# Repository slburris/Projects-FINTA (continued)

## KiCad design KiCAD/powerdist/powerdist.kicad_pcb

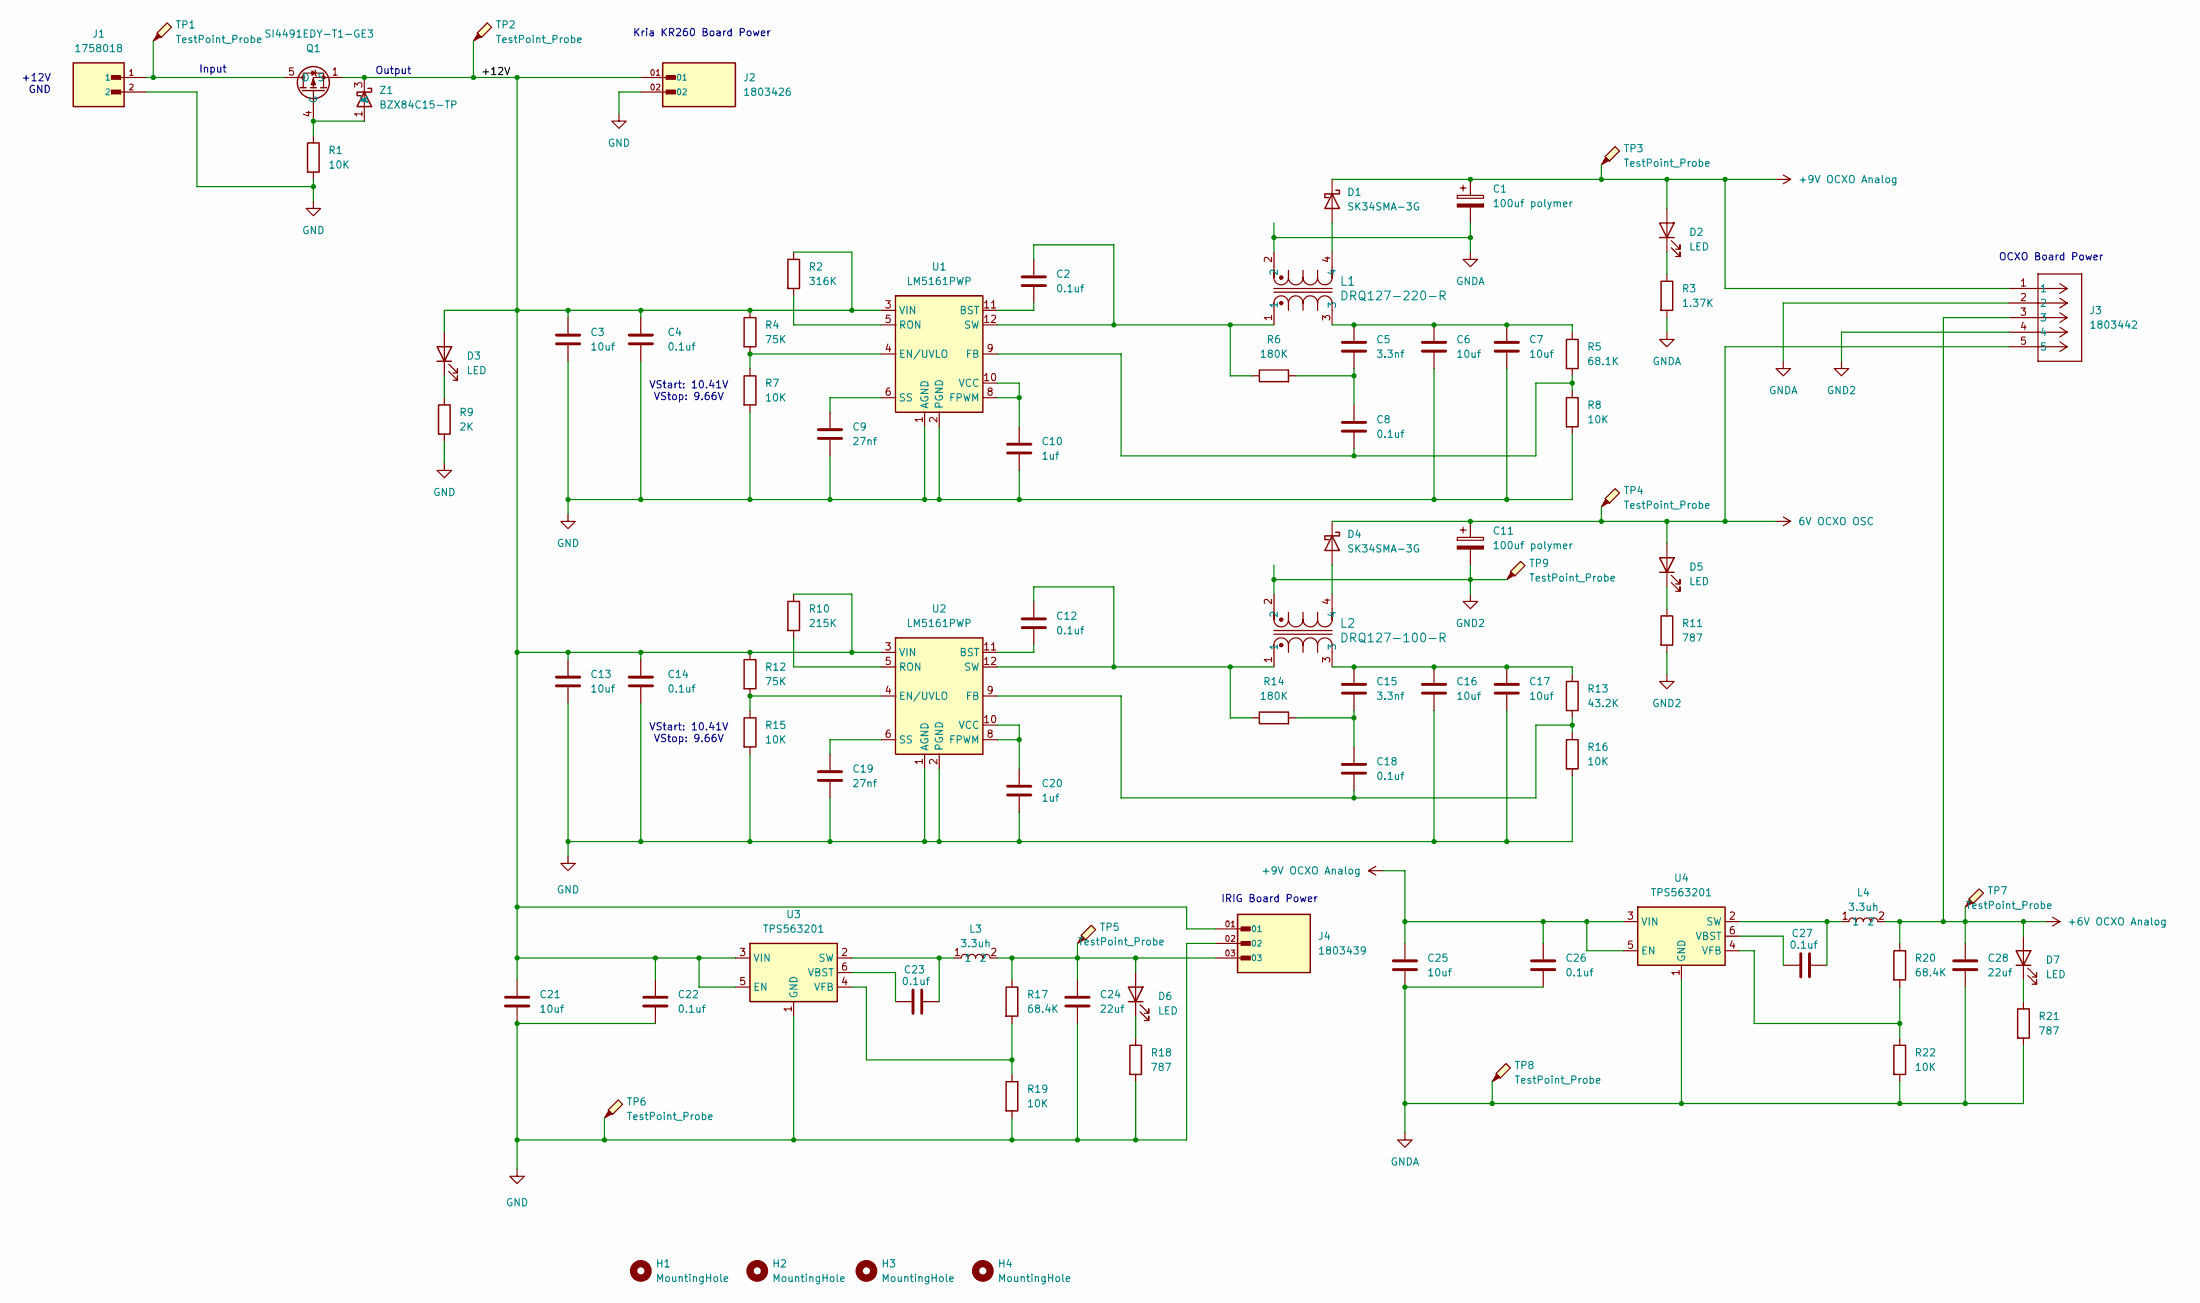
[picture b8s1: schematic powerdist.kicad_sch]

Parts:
C1, C11: 100uf polymer; CP_Radial_D5.0mm_P2.00mm
C2, C8, C12, C18: 0.1uf; C_0603_1608Metric_Pad1.08x0.95mm_HandSolder
C3, C6, C7, C13, C16, C17, C21, C25: 10uf; C_1206_3216Metric_Pad1.33x1.80mm_HandSolder
C4, C14, C22, C23, C26, C27: 0.1uf; C_1206_3216Metric_Pad1.33x1.80mm_HandSolder
C5, C15: 3.3nf; C_0603_1608Metric_Pad1.08x0.95mm_HandSolder
C9, C19: 27nf; C_0603_1608Metric_Pad1.08x0.95mm_HandSolder
C10, C20: 1uf; C_0603_1608Metric_Pad1.08x0.95mm_HandSolder
C24, C28: 22uf; C_1206_3216Metric_Pad1.33x1.80mm_HandSolder
D1, D4: SK34SMA-3G; D_SMA-SMB_Universal_Handsoldering
D2, D3, D5, D6, D7: LED; LED_0805_2012Metric_Pad1.15x1.40mm_HandSolder
H1, H2, H3, H4: MountingHole; MountingHole_5.3mm_M5
J1: 1758018; PHOENIX_1758018; PARTREV 10.07.2018
J2: 1803426; PHOENIX_1803426; PARTREV 25.02.2015
J3: 1803442; CONN_1803455; PARTREV 25.02.2015
J4: 1803439; PHOENIX_1803439; PARTREV 25.02.2015
L1: DRQ127-220-R; DRQ127
L2: DRQ127-100-R; DRQ127
L3, L4: 3.3uh; BCIHP10SC
Q1: SI4491EDY-T1-GE3; SOIC127P600X175-8N; Manufacturer_Part_Number SI4491EDY-T1-GE3
R1, R19, R22: 10K; R_1206_3216Metric_Pad1.30x1.75mm_HandSolder
R2: 316K; R_0603_1608Metric_Pad0.98x0.95mm_HandSolder
R3: 1.37K; R_1206_3216Metric_Pad1.30x1.75mm_HandSolder
R4, R12: 75K; R_0603_1608Metric_Pad0.98x0.95mm_HandSolder
R5: 68.1K; R_0603_1608Metric_Pad0.98x0.95mm_HandSolder
R6, R14: 180K; R_0603_1608Metric_Pad0.98x0.95mm_HandSolder
R7, R8, R15: 10K; R_0603_1608Metric_Pad0.98x0.95mm_HandSolder
R9: 2K; R_1206_3216Metric_Pad1.30x1.75mm_HandSolder
R10: 215K; R_0603_1608Metric_Pad0.98x0.95mm_HandSolder
R11, R18, R21: 787; R_1206_3216Metric_Pad1.30x1.75mm_HandSolder
R13: 43.2K; R_0805_2012Metric_Pad1.20x1.40mm_HandSolder
R16: 10K; R_0805_2012Metric_Pad1.20x1.40mm_HandSolder
R17, R20: 68.4K; R_1206_3216Metric_Pad1.30x1.75mm_HandSolder
TP1, TP2, TP3, TP4, TP5, TP6, TP7, TP8, TP9: TestPoint_Probe; TestPoint_Pad_2.0x2.0mm
U1, U2: LM5161PWP; Texas_HTSSOP-14-1EP_4.4x5mm_P0.65mm_EP3.4x5mm_Mask3.155x3.2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
U3, U4: TPS563201; SOT-23-6
Z1: BZX84C15-TP; SOT95P237X125-3N; Mouser Part Number 833-BZX84C15-TP

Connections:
6V OCXO OSC: C11.1, D4.1 (K), D5.2 (A), J3.5, TP4.1
+6V OCXO Analog: C28.1, D7.2 (A), J3.3, L4.2, R20.1, TP7.1
+9V OCXO Analog: C1.1, C25.1, C26.1, D1.1 (K), D2.2 (A), J3.1, TP3.1, U4.3 (VIN), U4.5 (EN)
/+12V: C3.1, C4.1, C13.1, C14.1, C21.1, C22.1, D3.2 (A), J2.01, J4.01, Q1.1 (S), Q1.2 (S), Q1.3 (S), R2.1, R4.1, R10.1, R12.1, TP2.1, U1.3 (VIN), U2.3 (VIN), U3.3 (VIN), U3.5 (EN), Z1.3 (K)
GND: C3.2, C4.2, C6.2, C7.2, C9.2, C10.2, C13.2, C14.2, C16.2, C17.2, C19.2, C20.2, C21.2, C22.2, C24.2, J1.2, J2.02, J4.02, R1.2, R7.2, R8.2, R9.2, R15.2, R16.2, R18.2, R19.2, TP6.1, U1.1 (AGND), U1.2 (PGND), U1.15 (AGND), U2.1 (AGND), U2.2 (PGND), U2.15 (AGND), U3.1 (GND)
GND2: C11.2, J3.4, L2.2, R11.2, TP9.1
GNDA: C1.2, C25.2, C26.2, C28.2, J3.2, L1.2, R3.2, R21.2, R22.2, TP8.1, U4.1 (GND)
unnamed: C2.1, L1.1, R6.1, U1.12 (SW), U1.13 (SW)
unnamed: C5.1, C6.1, C7.1, L1.3, R5.1
unnamed: C5.2, C8.1, R6.2
unnamed: C12.1, L2.1, R14.1, U2.12 (SW), U2.13 (SW)
unnamed: C15.1, C16.1, C17.1, L2.3, R13.1
unnamed: C15.2, C18.1, R14.2
unnamed: D1.2 (A), L1.4
unnamed: D2.1 (K), R3.1
unnamed: D3.1 (K), R9.1
unnamed: D4.2 (A), L2.4
unnamed: D5.1 (K), R11.1
unnamed: C24.1, D6.2 (A), J4.03, L3.2, R17.1, TP5.1
unnamed: D6.1 (K), R18.1
unnamed: D7.1 (K), R21.1
unnamed: J1.1, Q1.5 (D), Q1.6 (D), Q1.7 (D), Q1.8 (D), TP1.1
unnamed: Q1.4 (G), R1.1, Z1.1 (A)
unnamed: C2.2, U1.11 (BST)
unnamed: R4.2, R7.1, U1.4 (EN/UVLO)
unnamed: C8.2, R5.2, R8.1, U1.9 (FB)
unnamed: C10.1, U1.8 (FPWM), U1.10 (VCC)
unnamed: R2.2, U1.5 (RON)
unnamed: C9.1, U1.6 (SS)
unnamed: C12.2, U2.11 (BST)
unnamed: R12.2, R15.1, U2.4 (EN/UVLO)
unnamed: C18.2, R13.2, R16.1, U2.9 (FB)
unnamed: C20.1, U2.8 (FPWM), U2.10 (VCC)
unnamed: R10.2, U2.5 (RON)
unnamed: C19.1, U2.6 (SS)
unnamed: C23.2, L3.1, U3.2 (SW)
unnamed: C23.1, U3.6 (VBST)
unnamed: R17.2, R19.1, U3.4 (VFB)
unnamed: C27.2, L4.1, U4.2 (SW)
unnamed: C27.1, U4.6 (VBST)
unnamed: R20.2, R22.1, U4.4 (VFB)

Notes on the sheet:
Input
OCXO Board Power
Kria KR260 Board Power
+12V GND
Output
VStart: 10.41V VStop: 9.66V
IRIG Board Power

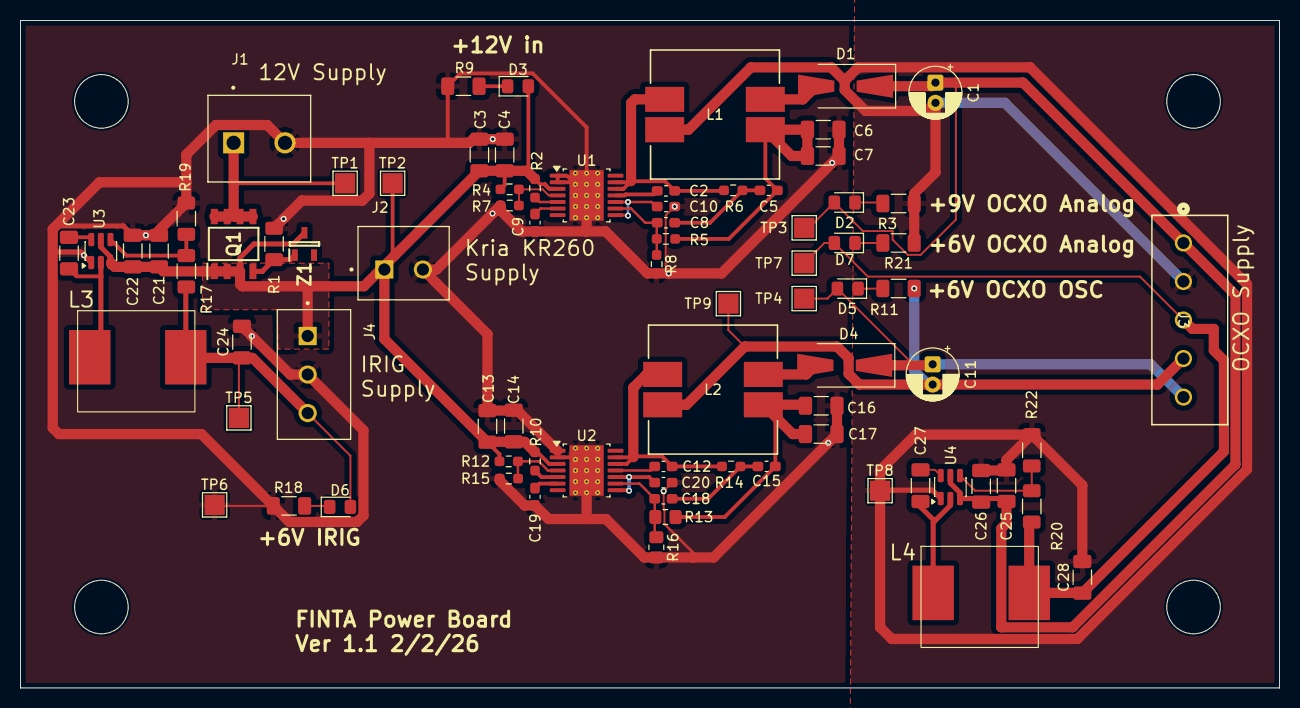
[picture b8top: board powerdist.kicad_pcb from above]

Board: 2 copper layers, 124.5 x 66.0 mm, 84 parts (0 on the bottom side), 41 nets.

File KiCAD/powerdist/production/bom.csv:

Designator,Footprint,Quantity,Value,LCSC Part #
"C1, C11",CP_Radial_D5.0mm_P2.00mm,2,100uf polymer,
"C10, C20",0603,2,1uf,
"C12, C18, C2, C8",0603,4,0.1uf,
"C13, C16, C17, C21, C25, C3, C6, C7",1206,8,10uf,
"C14, C22, C23, C26, C27, C4",1206,6,0.1uf,
"C15, C5",0603,2,3.3nf,
"C19, C9",0603,2,27nf,
"C24, C28",1206,2,22uf,
"D1, D4",D_SMA-SMB_Universal_Handsoldering,2,SK34SMA-3G,
"D2, D3, D5, D6, D7",0805,5,LED,
J1,PHOENIX_1758018,1,1758018,
J2,PHOENIX_1803426,1,1803426,
J3,CONN_1803455,1,1803442,
J4,PHOENIX_1803439,1,1803439,
L1,DRQ127,1,DRQ127-220-R,
L2,DRQ127,1,DRQ127-100-R,
"L3, L4",BCIHP10SC,2,3.3uh,
Q1,SOIC127P600X175-8N,1,SI4491EDY-T1-GE3,
"R1, R19, R22",1206,3,10K,
R10,0603,1,215K,
"R11, R18, R21",1206,3,787,
"R12, R4",0603,2,75K,
R13,0805,1,43.2K,
"R14, R6",0603,2,180K,
"R15, R7, R8",0603,3,10K,
R16,0805,1,10K,
"R17, R20",1206,2,68.4K,
R2,0603,1,316K,
R3,1206,1,1.37K,
R5,0603,1,68.1K,
R9,1206,1,2K,
"TP1, TP2, TP3, TP4, TP5, TP6, TP7, TP8, TP9",TestPoint_Pad_2.0x2.0mm,9,TestPoint_Probe,
"U1, U2",Texas_HTSSOP-14-1EP_4.4x5mm_P0.65mm_EP3.4x5mm_Mask3.155x3.255mm_ThermalVias,2,LM5161PWP,
"U3, U4",SOT-23-6,2,TPS563201,
Z1,SOT95P237X125-3N,1,BZX84C15-TP,

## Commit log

2026-02-05 more init
2026-02-15 before switchover to new daughtercard format
2026-02-22 Reworked, now with IRIG option board complete
2026-02-25 Rework to real version 1.0, with separate GPS, OCXO, and IRIG boards
2026-02-27 Added FPGA debug header and debug LEDs
2026-03-26 gps PCB 1.1
2026-03-30 ocxo board 1.1, with fixes for the major errors
2026-05-14 OCXO board 1.1
2026-05-15 LDO daughterboard 1.1
